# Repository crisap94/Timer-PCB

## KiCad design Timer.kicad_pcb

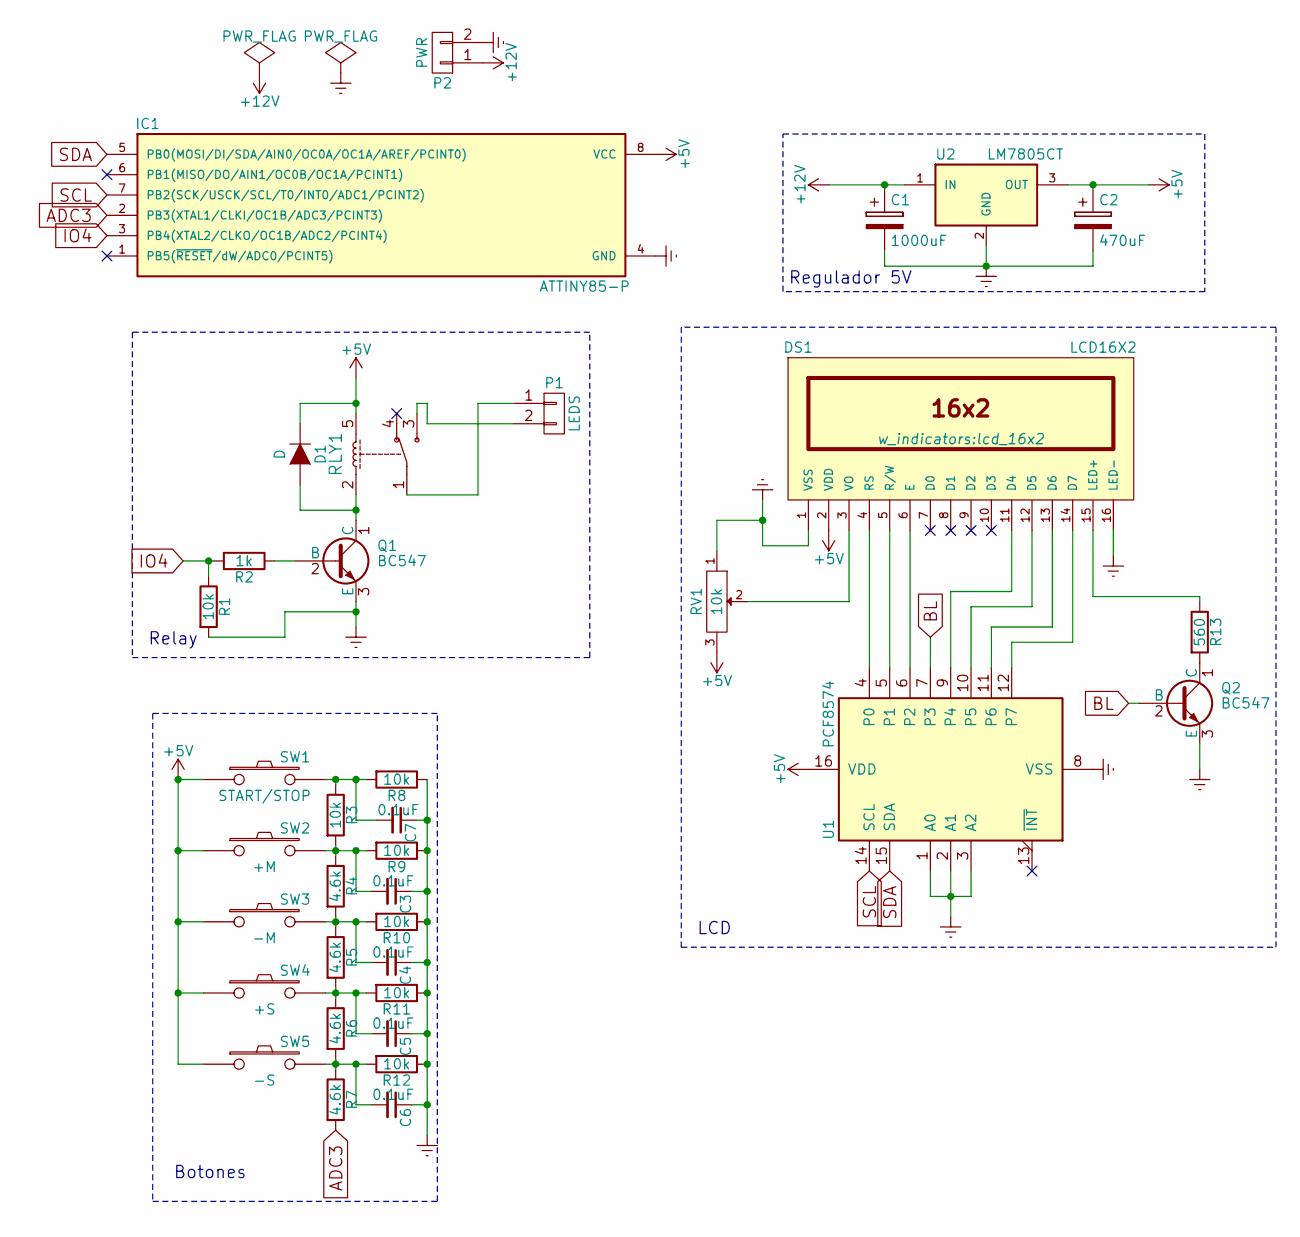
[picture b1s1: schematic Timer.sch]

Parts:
C1: 1000uF; CP_8x11.5mm
C2: 470uF; CP_8x11.5mm
C3, C4, C5, C6, C7: 0.1uF; cnp_3mm_disc
D1: D; diode_do35
DS1: LCD16X2; lcd_16x2
IC1: ATTINY85-P; dil_8-300_socket
P1: LEDS; mors_2p
P2: PWR; mors_2p
Q1, Q2: BC547; TO-92_Inline_Wide
R1, R3, R8, R9, R10, R11, R12: 10k; RC03
R2: 1k; RC03
R4, R5, R6, R7: 4.6k; RC03
R13: 560; RC03
RLY1: RELAY_HJR-3FF_Z; relay_hjr-3ff_z
RV1: 10k; trimmer_piher_pt6xv
SW1: START/STOP; PCB_PUSH
SW2: +M; PCB_PUSH
SW3: -M; PCB_PUSH
SW4: +S; PCB_PUSH
SW5: -S; PCB_PUSH
U1: PCF8574; dil_16-300_socket
U2: LM7805CT; TO-220_Neutral123_Horizontal_LargePads

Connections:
+5V: C2.1, D1.1 (K), DS1.2 (VDD), IC1.8 (VCC), RLY1.5, RV1.3, SW1.1, SW2.1, SW3.1, SW4.1, SW5.1, U1.16 (VDD), U2.3 (OUT)
+12V: C1.1, P2.1, U2.1 (IN)
ADC3: IC1.2 (PB3(XTAL1/CLKI/OC1B/ADC3/PCINT3)), R7.2
BL: Q2.2 (B), U1.7 (P3)
Earth: C1.2, C2.2, C3.1, C4.1, C5.1, C6.1, C7.1, DS1.1 (VSS), DS1.16 (LED-), IC1.4 (GND), P2.2, Q1.3 (E), Q2.3 (E), R1.2, R8.1, R9.1, R10.1, R11.1, R12.1, RV1.1, U1.1 (A0), U1.2 (A1), U1.3 (A2), U1.8 (VSS), U2.2 (GND)
IO4: IC1.3 (PB4(XTAL2/CLKO/OC1B/ADC2/PCINT4)), R1.1, R2.2
unnamed: C3.2, R3.2, R4.1, R9.2, SW2.2
unnamed: C4.2, R4.2, R5.1, R10.2, SW3.2
unnamed: C5.2, R5.2, R6.1, R11.2, SW4.2
unnamed: C6.2, R6.2, R7.1, R12.2, SW5.2
unnamed: C7.2, R3.1, R8.2, SW1.2
unnamed: D1.2 (A), Q1.1 (C), RLY1.2
unnamed: DS1.3 (VO), RV1.2
unnamed: DS1.4 (RS), U1.4 (P0)
unnamed: DS1.5 (R/W), U1.5 (P1)
unnamed: DS1.6 (E), U1.6 (P2)
unnamed: DS1.11 (D4), U1.9 (P4)
unnamed: DS1.12 (D5), U1.10 (P5)
unnamed: DS1.13 (D6), U1.11 (P6)
unnamed: DS1.14 (D7), U1.12 (P7)
unnamed: DS1.15 (LED+), R13.1
unnamed: P1.1, RLY1.1
unnamed: P1.2, RLY1.3
unnamed: Q1.2 (B), R2.1
unnamed: Q2.1 (C), R13.2
SCL: IC1.7 (PB2(SCK/USCK/SCL/T0/INT0/ADC1/PCINT2)), U1.14 (SCL)
SDA: IC1.5 (PB0(MOSI/DI/SDA/AIN0/OC0A/OC1A/AREF/PCI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), U1.15 (SDA)

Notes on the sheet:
Regulador 5V
LCD
Relay
Botones

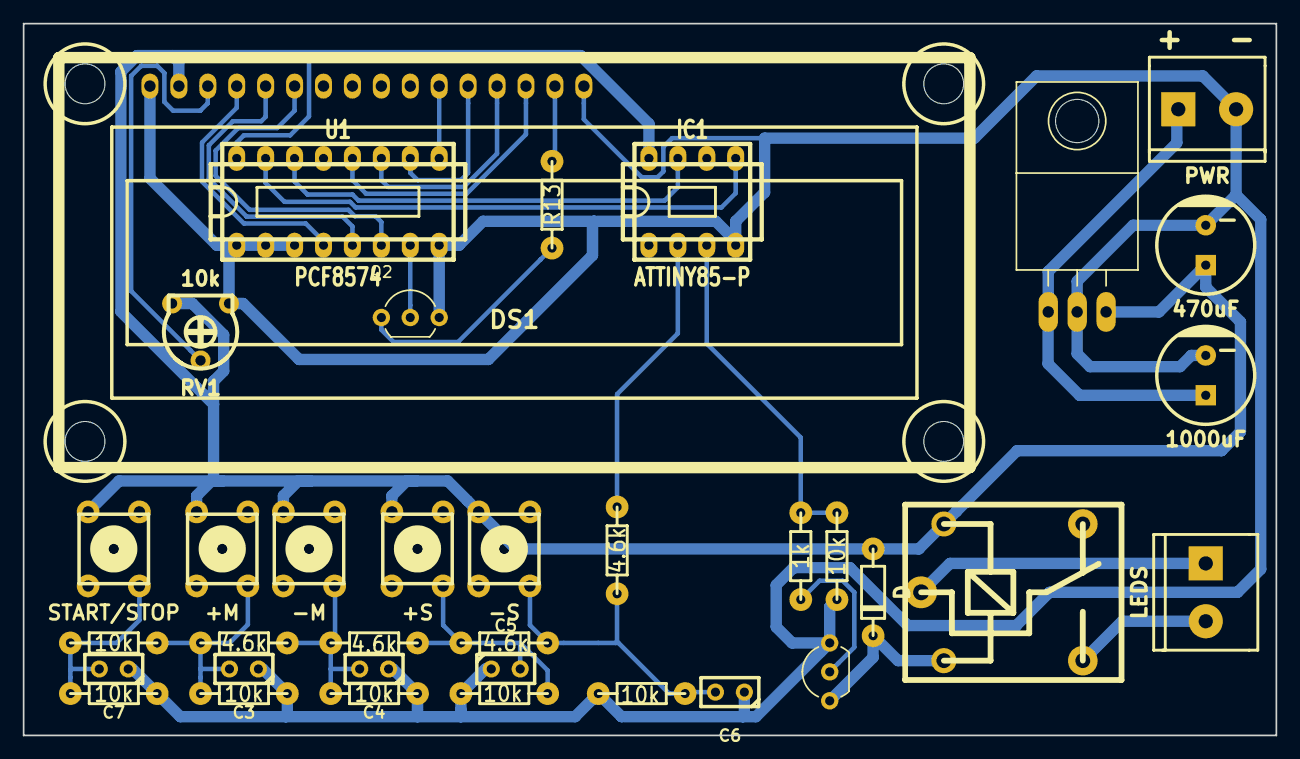
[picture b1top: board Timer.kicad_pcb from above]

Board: 2 copper layers, 110.0 x 62.5 mm, 36 parts (0 on the bottom side), 27 nets.

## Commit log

2016-02-29 :confetti_ball: Added .gitattributes & .gitignore files
2016-02-29 Finished
2016-02-29 Updated PCB
2016-03-01 Some Photos Added
2016-03-01 Cleaning the View
    removing some Package names for a better view of the sch.
